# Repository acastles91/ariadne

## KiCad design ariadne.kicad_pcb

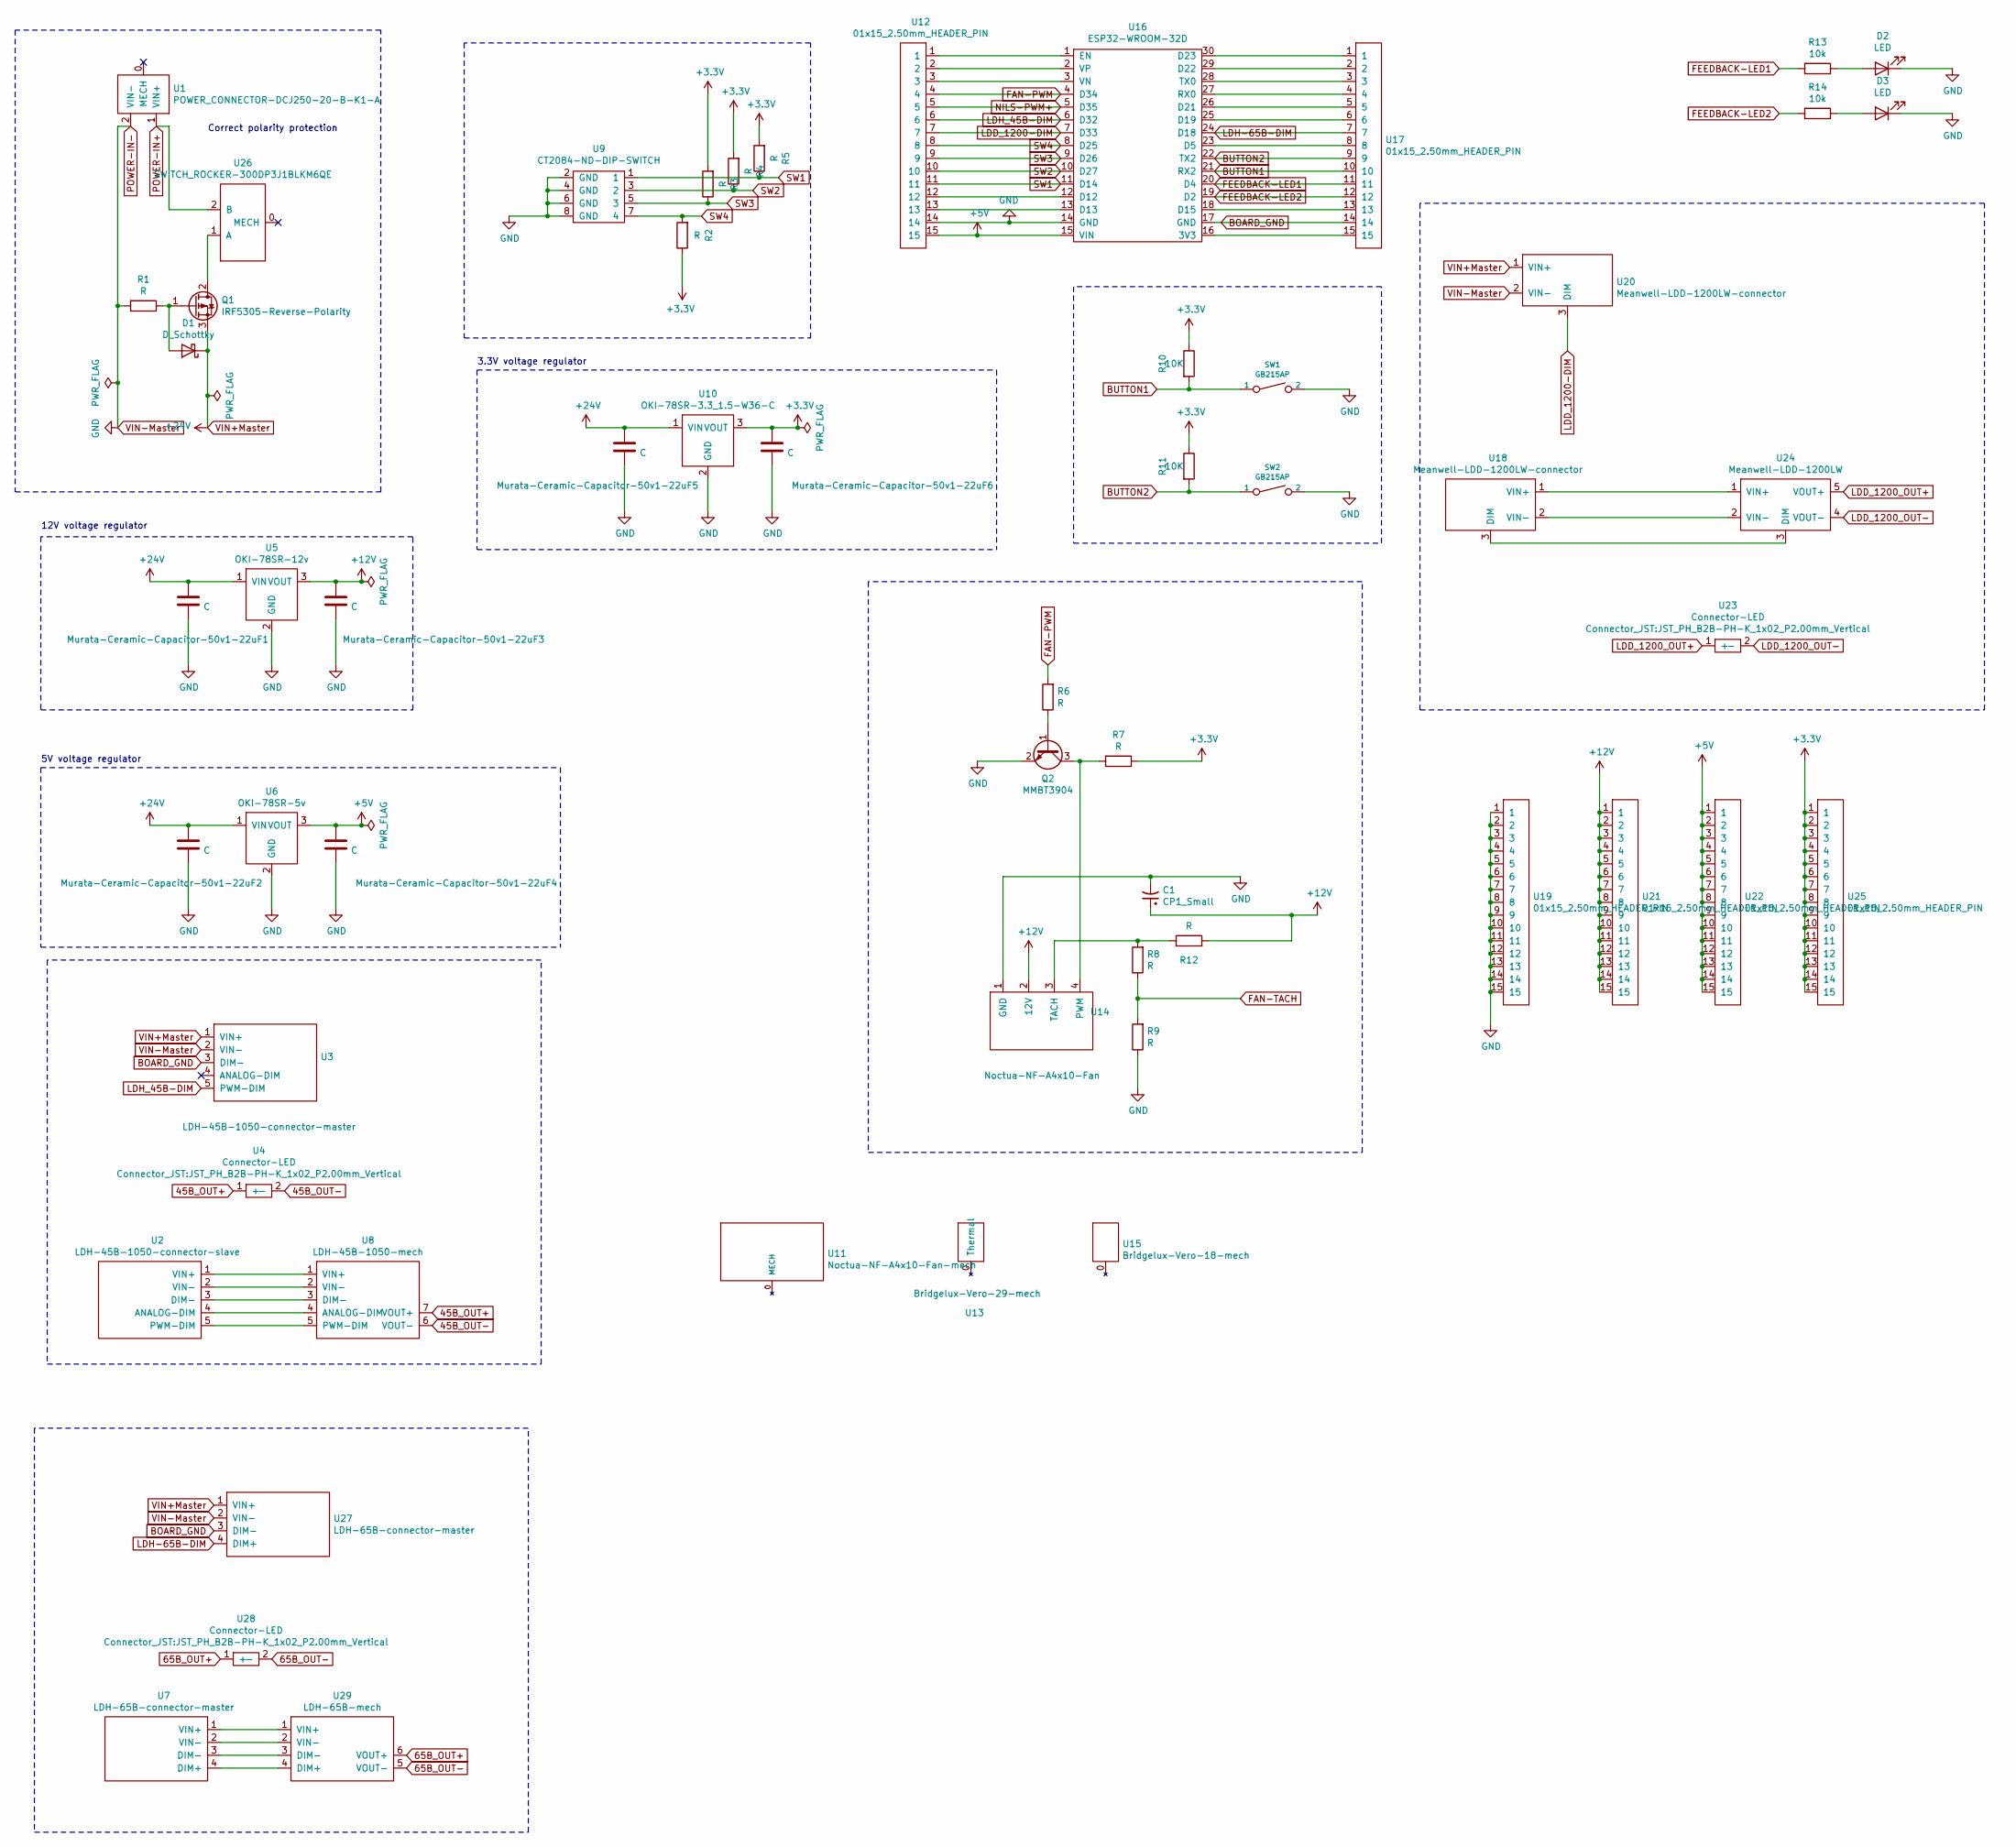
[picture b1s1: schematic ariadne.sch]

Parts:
C1: CP1_Small; CP_Radial_D5.0mm_P2.00mm
D1: D_Schottky; D_DO-41_SOD81_P7.62mm_Horizontal
D2, D3: LED; LED_D3.0mm_Horizontal_O1.27mm_Z2.0mm
Murata-Ceramic-Capacitor-50v1-22uF1, Murata-Ceramic-Capacitor-50v1-22uF2, Murata-Ceramic-Capacitor-50v1-22uF3, Murata-Ceramic-Capacitor-50v1-22uF4, Murata-Ceramic-Capacitor-50v1-22uF5, Murata-Ceramic-Capacitor-50v1-22uF6: C; C_Disc_D3.0mm_W1.6mm_P2.50mm
Q1: IRF5305-Reverse-Polarity; TO-220-3_Horizontal_TabDown
Q2: MMBT3904; TO-92
R1, R2, R3, R4, R5, R6, R7, R8, R9, R12: R; R_Axial_DIN0204_L3.6mm_D1.6mm_P7.62mm_Horizontal
R10, R11: 10K; R_Axial_DIN0204_L3.6mm_D1.6mm_P7.62mm_Horizontal
R13, R14: 10k; R_Axial_DIN0204_L3.6mm_D1.6mm_P7.62mm_Horizontal
SW1, SW2: GB215AP
U1: POWER_CONNECTOR-DCJ250-20-B-K1-A; POWER_JACK_DCJ250-20-B-K1-A
U2: LDH-45B-1050-connector-slave; Molex_Micro-Fit_3.0_43650-0500_1x05_P3.00mm_Horizontal
U3: LDH-45B-1050-connector-master; Molex_Micro-Fit_3.0_43650-0500_1x05_P3.00mm_Horizontal
U4, U23, U28: Connector-LED; JST_PH_B2B-PH-K_1x02_P2.00mm_Vertical
U5: OKI-78SR-12v; Converter_DCDC_muRata_OKI-78SR_Vertical
U6: OKI-78SR-5v; Converter_DCDC_muRata_OKI-78SR_Vertical
U7, U27: LDH-65B-connector-master; Molex_Micro-Fit_3.0_43650-0400_1x04_P3.00mm_Horizontal
U8: LDH-45B-1050-mech; MeanWell-LDH-45B-1050-ariadne
U9: CT2084-ND-DIP-SWITCH; SW_DIP_SPSTx04_Piano_CTS_Series194-4MSTN_W7.62mm_P2.54mm
U10: OKI-78SR-3.3_1.5-W36-C; Converter_DCDC_muRata_OKI-78SR_Vertical
U11: Noctua-NF-A4x10-Fan-mech; Noctua-NF-A4x10
U12, U17, U19, U21, U22, U25: 01x15_2.50mm_HEADER_PIN; PinHeader_1x15_P2.54mm_Vertical
U13: Bridgelux-Vero-29-mech; Vero-29-mech
U14: Noctua-NF-A4x10-Fan; Molex_Micro-Fit_3.0_43650-0400_1x04_P3.00mm_Horizontal
U15: Bridgelux-Vero-18-mech; Vero-18-mech
U16: ESP32-WROOM-32D; ESP32-DEVKIT
U18, U20: Meanwell-LDD-1200LW-connector; Molex_Micro-Fit_3.0_43650-0300_1x03_P3.00mm_Horizontal
U24: Meanwell-LDD-1200LW; Meanwell-LDD-1xxxL
U26: SWITCH_ROCKER-300DP3J1BLKM6QE
U29: LDH-65B-mech; MeanWell-LDH-65

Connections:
45B_OUT+: U4.1 (+), U8.7 (VOUT+)
45B_OUT-: U4.2 (-), U8.6 (VOUT-)
65B_OUT+: U28.1 (+), U29.6 (VOUT+)
65B_OUT-: U28.2 (-), U29.5 (VOUT-)
+3V3: Murata-Ceramic-Capacitor-50v1-22uF6.1, R2.1, R3.2, R4.2, R5.2, R7.1, R10.1, R11.1, U10.3 (VOUT), U25.1, U25.2, U25.3, U25.4, U25.5, U25.6, U25.7, U25.8, U25.9, U25.10, U25.11, U25.12, U25.13, U25.14, U25.15; also elsewhere on the board
+5V: Murata-Ceramic-Capacitor-50v1-22uF4.1, U6.3 (VOUT), U12.15, U16.15 (VIN), U22.1, U22.2, U22.3, U22.4, U22.5, U22.6, U22.7, U22.8, U22.9, U22.10, U22.11, U22.12, U22.13, U22.14, U22.15; also elsewhere on the board
+12V: C1.1, Murata-Ceramic-Capacitor-50v1-22uF3.1, R12.2, U5.3 (VOUT), U14.2 (12V), U21.1, U21.2, U21.3, U21.4, U21.5, U21.6, U21.7, U21.8, U21.9, U21.10, U21.11, U21.12, U21.13, U21.14, U21.15; also elsewhere on the board
BOARD_GND: U3.3 (DIM-), U16.17 (GND), U17.14, U27.3 (DIM-)
BUTTON1: R10.2, SW1.1, U16.21 (RX2), U17.10
BUTTON2: R11.2, SW2.1, U16.22 (TX2), U17.9
FAN-PWM: R6.2, U12.4, U16.4 (D34)
FAN-TACH: R8.1, R9.2
FEEDBACK-LED1: R13.2, U16.20 (D4), U17.11
FEEDBACK-LED2: R14.2, U16.19 (D2), U17.12
LDD_1200-DIM: U12.7, U16.7 (D33), U20.3 (DIM)
LDD_1200_OUT+: U23.1 (+), U24.5 (VOUT+)
LDD_1200_OUT-: U23.2 (-), U24.4 (VOUT-)
LDH-65B-DIM: U16.24 (D18), U17.7, U27.4 (DIM+)
LDH_45B-DIM: U3.5 (PWM-DIM), U12.6, U16.6 (D32)
NILS-PWM+: U12.5, U16.5 (D35)
unnamed: D1.2 (A), Q1.1 (G), R1.1
unnamed: D2.2 (A), R13.1
unnamed: D3.2 (A), R14.1
unnamed: Q1.2 (D), U26.1 (A)
unnamed: Q2.1 (B), R6.1
unnamed: Q2.3 (C), R7.2, U14.4 (PWM)
unnamed: R8.2, R12.1, U14.3 (TACH)
unnamed: U2.1 (VIN+), U8.1 (VIN+)
unnamed: U2.2 (VIN-), U8.2 (VIN-)
unnamed: U2.3 (DIM-), U8.3 (DIM-)
unnamed: U2.4 (ANALOG-DIM), U8.4 (ANALOG-DIM)
unnamed: U2.5 (PWM-DIM), U8.5 (PWM-DIM)
unnamed: U12.1, U16.1 (EN)
unnamed: U12.2, U16.2 (VP)
unnamed: U12.3, U16.3 (VN)
unnamed: U12.12, U16.12 (D12)
unnamed: U12.13, U16.13 (D13)
unnamed: U16.16 (3V3), U17.15
unnamed: U16.18 (D15), U17.13
unnamed: U16.23 (D5), U17.8
unnamed: U16.25 (D19), U17.6
unnamed: U16.26 (D21), U17.5
unnamed: U16.27 (RX0), U17.4
unnamed: U16.28 (TX0), U17.3
unnamed: U16.29 (D22), U17.2
unnamed: U16.30 (D23), U17.1
unnamed: U18.1 (VIN+), U24.1 (VIN+)
unnamed: U18.2 (VIN-), U24.2 (VIN-)
unnamed: U18.3 (DIM), U24.3 (DIM)
unnamed: U7.1 (VIN+), U29.1 (VIN+)
unnamed: U7.2 (VIN-), U29.2 (VIN-)
unnamed: U7.3 (DIM-), U29.3 (DIM-)
unnamed: U7.4 (DIM+), U29.4 (DIM+)
POWER-IN+: U1.1 (VIN+), U26.2 (B)
POWER-IN-: C1.2, D2.1 (K), D3.1 (K), Murata-Ceramic-Capacitor-50v1-22uF1.2, Murata-Ceramic-Capacitor-50v1-22uF2.2, Murata-Ceramic-Capacitor-50v1-22uF3.2, Murata-Ceramic-Capacitor-50v1-22uF4.2, Murata-Ceramic-Capacitor-50v1-22uF5.2, Murata-Ceramic-Capacitor-50v1-22uF6.2, Q2.2 (E), R1.2, R9.1, SW1.2, SW2.2, U1.2 (VIN-), U3.2 (VIN-), U5.2 (GND), U6.2 (GND), U9.2 (GND), U9.4 (GND), U9.6 (GND), U9.8 (GND), U10.2 (GND), U12.14, U14.1 (GND), U16.14 (GND), U19.1, U19.2, U19.3, U19.4, U19.5, U19.6, U19.7, U19.8, U19.9, U19.10, U19.11, U19.12, U19.13, U19.14, U19.15, U20.2 (VIN-), U27.2 (VIN-); also elsewhere on the board
SW1: R5.1, U9.1, U12.11, U16.11 (D14)
SW2: R4.1, U9.3 (2), U12.10, U16.10 (D27)
SW3: R3.1, U9.5 (3), U12.9, U16.9 (D26)
SW4: R2.2, U9.7 (4), U12.8, U16.8 (D25)
VIN+Master: D1.1 (K), Murata-Ceramic-Capacitor-50v1-22uF1.1, Murata-Ceramic-Capacitor-50v1-22uF2.1, Murata-Ceramic-Capacitor-50v1-22uF5.1, Q1.3 (S), U3.1 (VIN+), U5.1 (VIN), U6.1 (VIN), U10.1 (VIN), U20.1 (VIN+), U27.1 (VIN+)

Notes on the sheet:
Correct polarity protection
12V voltage regulator
5V voltage regulator
3.3V voltage regulator

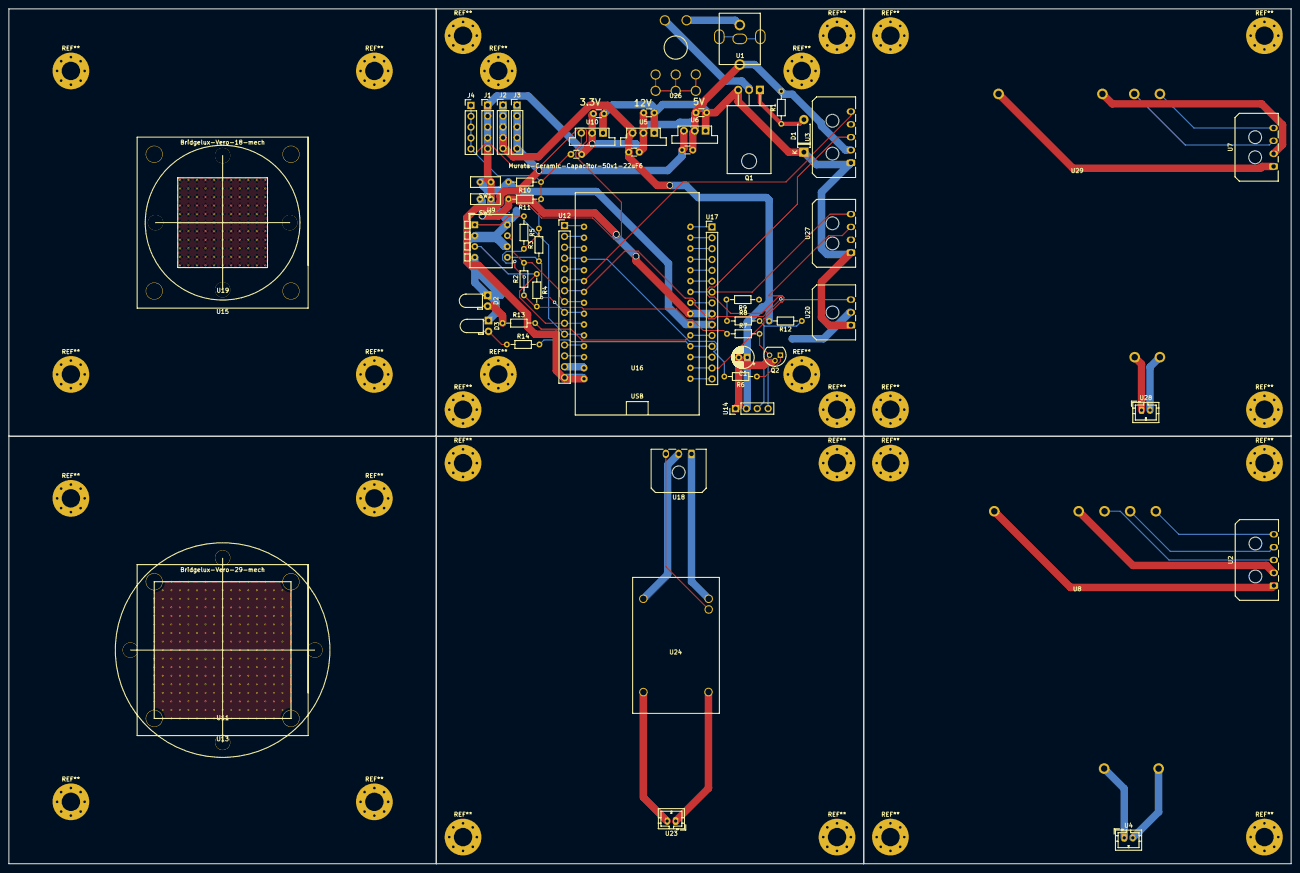
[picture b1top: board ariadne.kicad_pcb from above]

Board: 2 copper layers, 300.0 x 200.0 mm, 58 parts (0 on the bottom side), 60 nets.

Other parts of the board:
J1, J2, J3, J4: Conn_01x05_Male; PinHeader_1x05_P2.54mm_Vertical

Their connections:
+3V3: J4.1, J4.2, J4.3, J4.4, J4.5; also elsewhere on the board
+5V: J3.1, J3.2, J3.3, J3.4, J3.5; also elsewhere on the board
+12V: J2.1, J2.2, J2.3, J2.4, J2.5; also elsewhere on the board
POWER-IN-: J1.1, J1.2, J1.3, J1.4, J1.5; also elsewhere on the board

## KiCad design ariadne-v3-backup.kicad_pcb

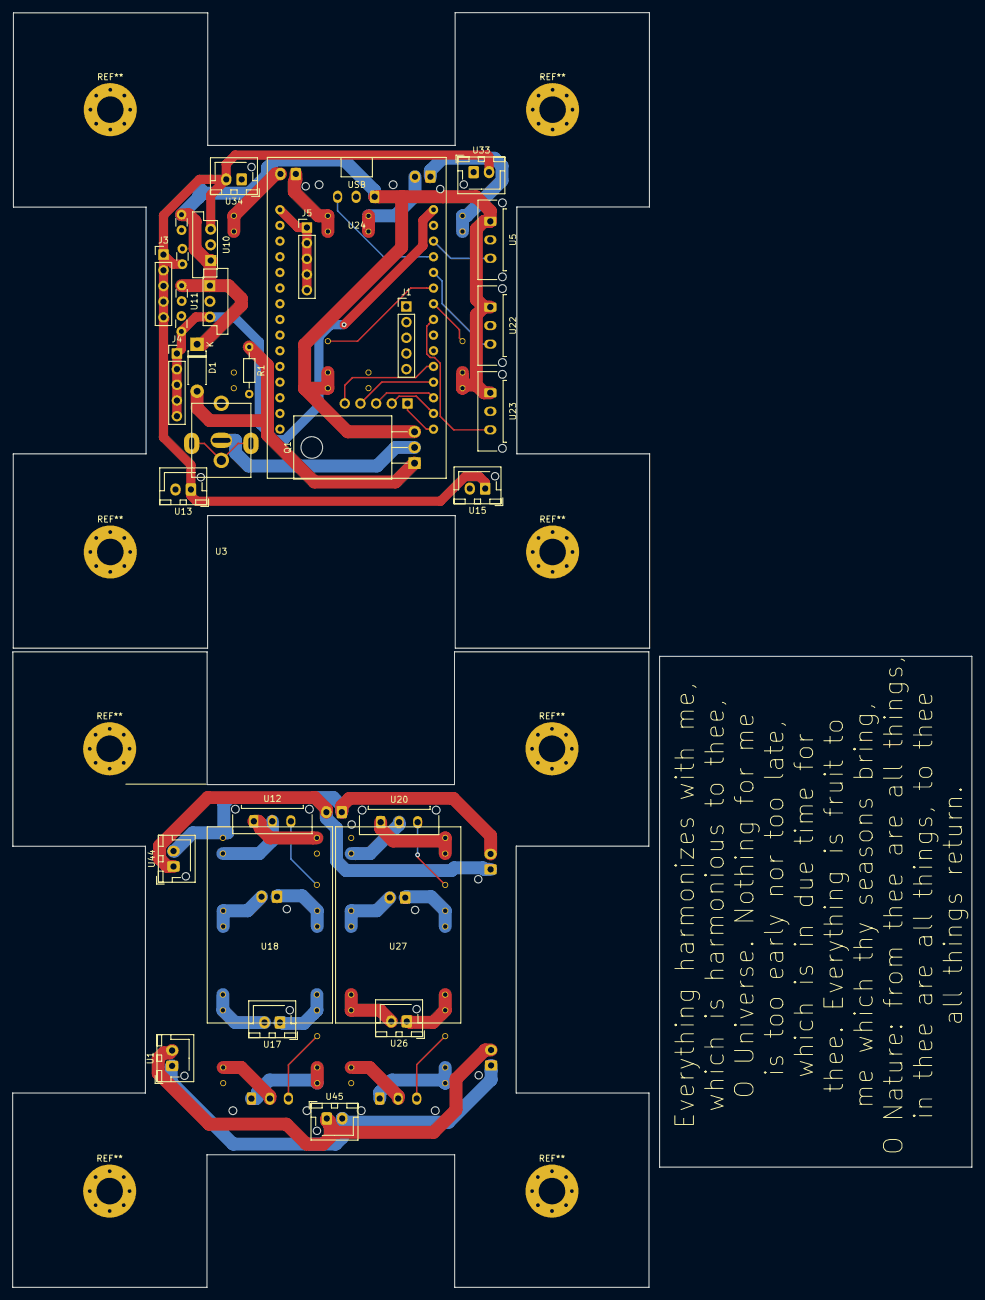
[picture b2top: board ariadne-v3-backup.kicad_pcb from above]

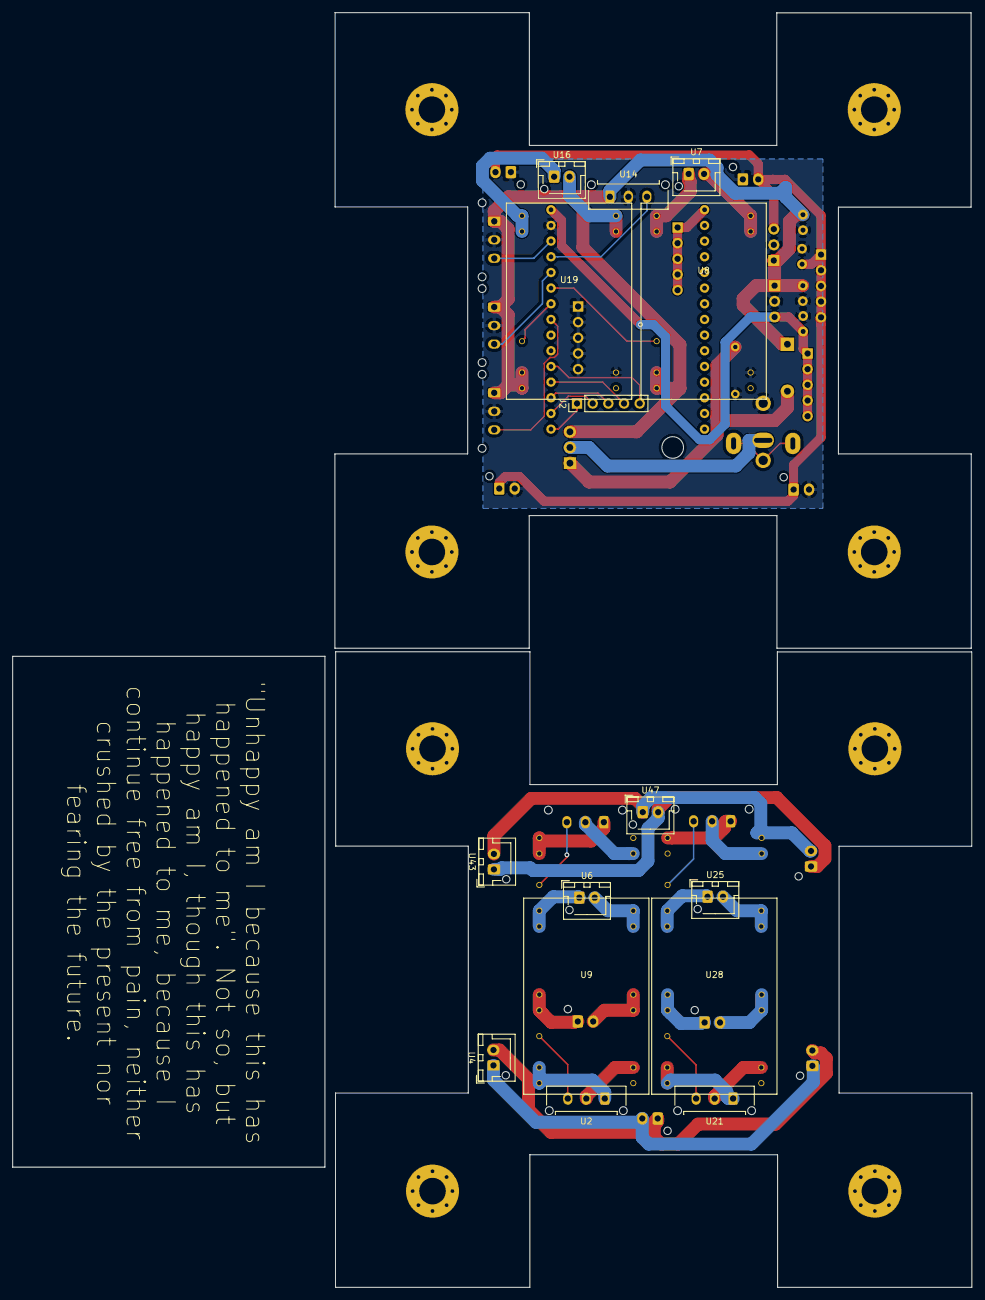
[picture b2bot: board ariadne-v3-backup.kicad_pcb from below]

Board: 2 copper layers, 155.5 x 206.6 mm, 46 parts (15 on the bottom side), 46 nets.

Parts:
D1: D_Zener-10V; D_DO-41_SOD81_P7.62mm_Horizontal
J1, J2, J3, J4, J5: Conn_01x05_Male; PinHeader_1x05_P2.54mm_Vertical
Murata-Ceramic-Capacitor-50v1-22uF1, Murata-Ceramic-Capacitor-50v1-22uF2, Murata-Ceramic-Capacitor-50v1-22uF3, Murata-Ceramic-Capacitor-50v1-22uF4: C; C_Disc_D3.0mm_W1.6mm_P2.50mm
Q1: IRF5305-Reverse-Polarity; TO-220-3_Horizontal_TabDown
R1: 100K; R_Axial_DIN0204_L3.6mm_D1.6mm_P7.62mm_Horizontal
U1, U4, U33, U34, U43, U44: Noctua-NF-A4x10-Simple-Fan-ariadne; JST_XH_B2B-XH-AM_1x02_P2.50mm_Vertical
U2, U5, U12, U14, U20, U21, U22, U23: Meanwell-LDD-1200LW-connector; Molex_Micro-Fit_3.0_43650-0315_1x03_P3.00mm_Vertical
U3: POWER_CONNECTOR-DCJ250-20-B-K1-A; POWER_JACK_DCJ250-20-B-K1-A
U6, U7, U16, U17, U25, U26: Connector-LED; JST_XH_B2B-XH-AM_1x02_P2.50mm_Vertical
U8, U9, U18, U19, U27, U28: Meanwell-LDD-1200LW; Meanwell-LDD-1xxxL
U10: OKI-78SR-12v; Converter_DCDC_muRata_OKI-78SR_Vertical
U11: OKI-78SR-5v; Converter_DCDC_muRata_OKI-78SR_Vertical
U13, U15: 12v-Connector; JST_XH_B2B-XH-AM_1x02_P2.50mm_Vertical
U24: ESP32-WROOM-32D; ESP32-DEVKIT
U45, U47: 12v-Connector_copy; JST_XH_B2B-XH-AM_1x02_P2.50mm_Vertical

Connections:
+3V3: J5.1, J5.2, J5.3, J5.4, J5.5, U24.16
+5V: J4.1, J4.2, J4.3, J4.4, J4.5, Murata-Ceramic-Capacitor-50v1-22uF4.1, U11.3, U24.15
+12V: J3.1, J3.2, J3.3, J3.4, J3.5, Murata-Ceramic-Capacitor-50v1-22uF3.1, U10.3, U13.1, U15.1, U33.2, U34.2
DIM-1: U5.3, U24.13
DIM-2: U14.3, U24.12
DIM-3: U22.3, U24.11
DIM-4: U8.21, U24.10
DIM-5: U19.21, U24.9
DIM-6: U23.3, U24.8
FAN1+: U43.2, U44.2, U47.1
FAN1-: U43.1, U44.1, U47.2
FAN2+: U1.2, U4.2, U45.1
FAN2-: U1.1, U4.1, U45.2
LDD_1-OUT+: U6.1, U9.13, U9.14
LDD_1-OUT-: U6.2, U9.11, U9.12
LDD_2-OUT+: U17.1, U18.13, U18.14
LDD_2-OUT-: U17.2, U18.11, U18.12
LDD_3-OUT+: U26.1, U27.13, U27.14
LDD_3-OUT-: U26.2, U27.11, U27.12
LDD_4-OUT+: U7.1, U8.13, U8.14
LDD_4-OUT-: U7.2, U8.11, U8.12
LDD_5-OUT+: U16.1, U19.13, U19.14
LDD_5-OUT-: U16.2, U19.11, U19.12
LDD_6-OUT+: U25.1, U28.13, U28.14
LDD_6-OUT-: U25.2, U28.11, U28.12
unnamed: D1.2, Q1.1, R1.1
unnamed: J2.1, U24.1
unnamed: J2.2, U24.2
unnamed: J2.3, U24.3
unnamed: J2.4, U24.4
unnamed: J2.5, U24.5
unnamed: U2.1, U9.23, U9.24
unnamed: U2.2, U9.2
unnamed: U2.3, U9.21
unnamed: U12.1, U18.23, U18.24
unnamed: U12.2, U18.2
unnamed: U12.3, U18.21
unnamed: U20.1, U27.23, U27.24
unnamed: U20.2, U27.2
unnamed: U20.3, U27.21
unnamed: U21.1, U28.23, U28.24
unnamed: U21.2, U28.2
unnamed: U21.3, U28.21
POWER-IN+: Q1.2, U3.1
POWER-IN-: J1.1, J1.2, J1.3, J1.4, J1.5, Murata-Ceramic-Capacitor-50v1-22uF1.2, Murata-Ceramic-Capacitor-50v1-22uF2.2, Murata-Ceramic-Capacitor-50v1-22uF3.2, Murata-Ceramic-Capacitor-50v1-22uF4.2, R1.2, U3.2, U5.2, U8.2, U10.2, U11.2, U13.2, U14.2, U15.2, U19.2, U22.2, U23.2, U24.14, U33.1, U34.1
VIN+Master1: D1.1, Murata-Ceramic-Capacitor-50v1-22uF1.1, Murata-Ceramic-Capacitor-50v1-22uF2.1, Q1.3, U5.1, U8.23, U8.24, U10.1, U11.1, U14.1, U19.23, U19.24, U22.1, U23.1

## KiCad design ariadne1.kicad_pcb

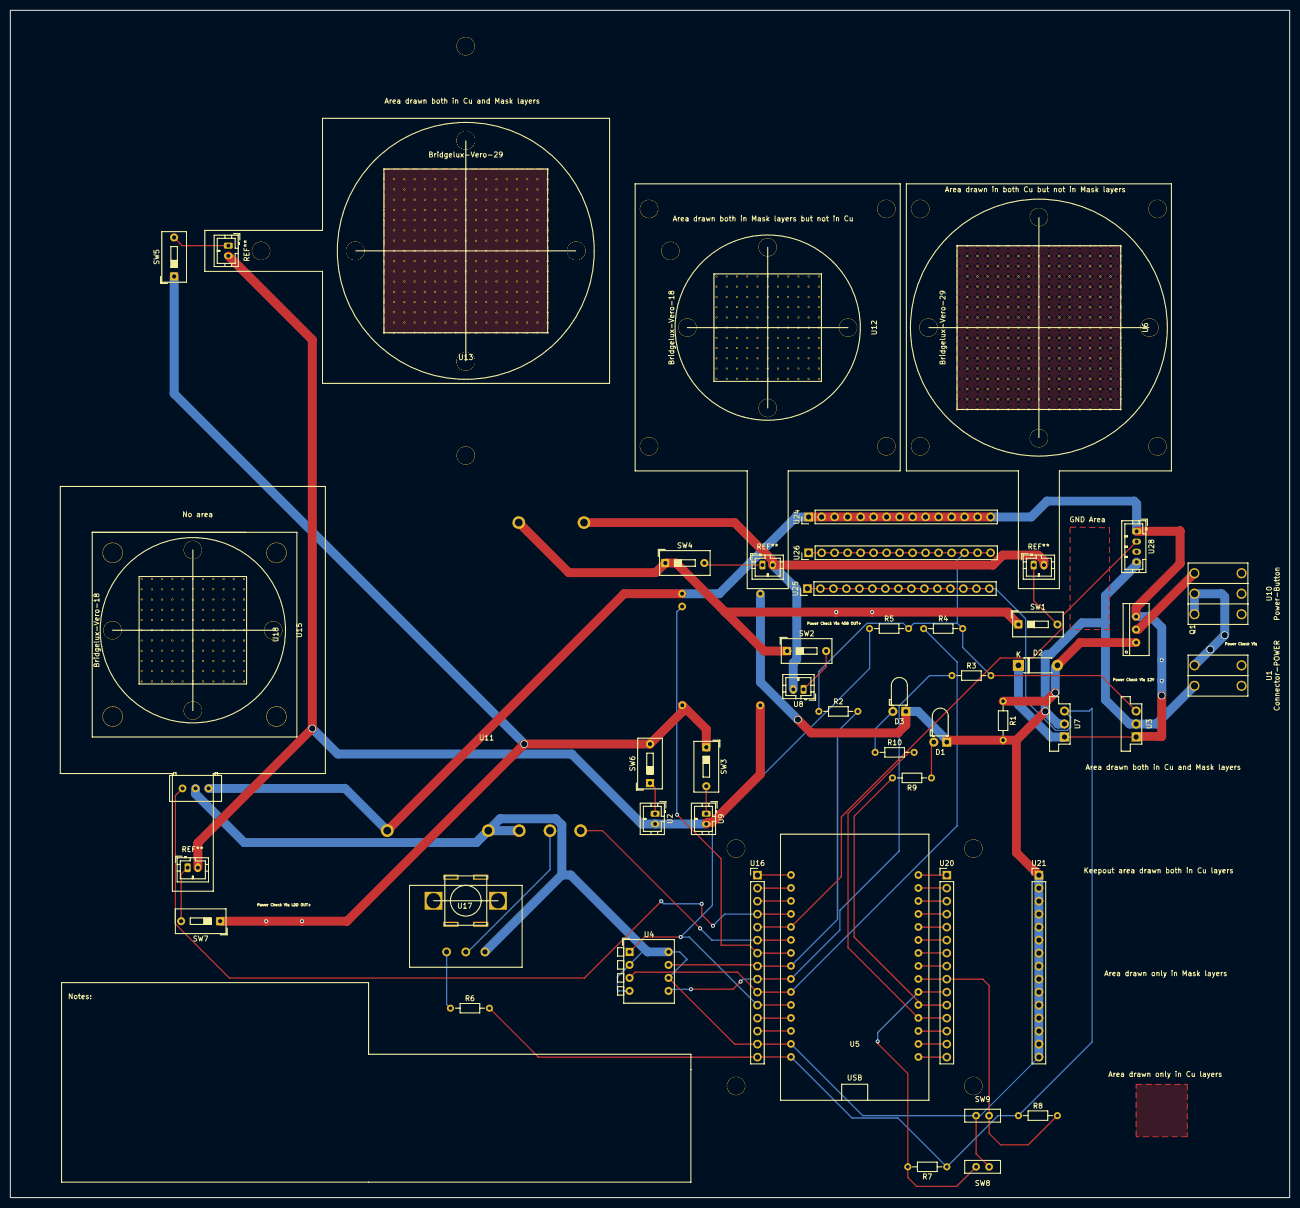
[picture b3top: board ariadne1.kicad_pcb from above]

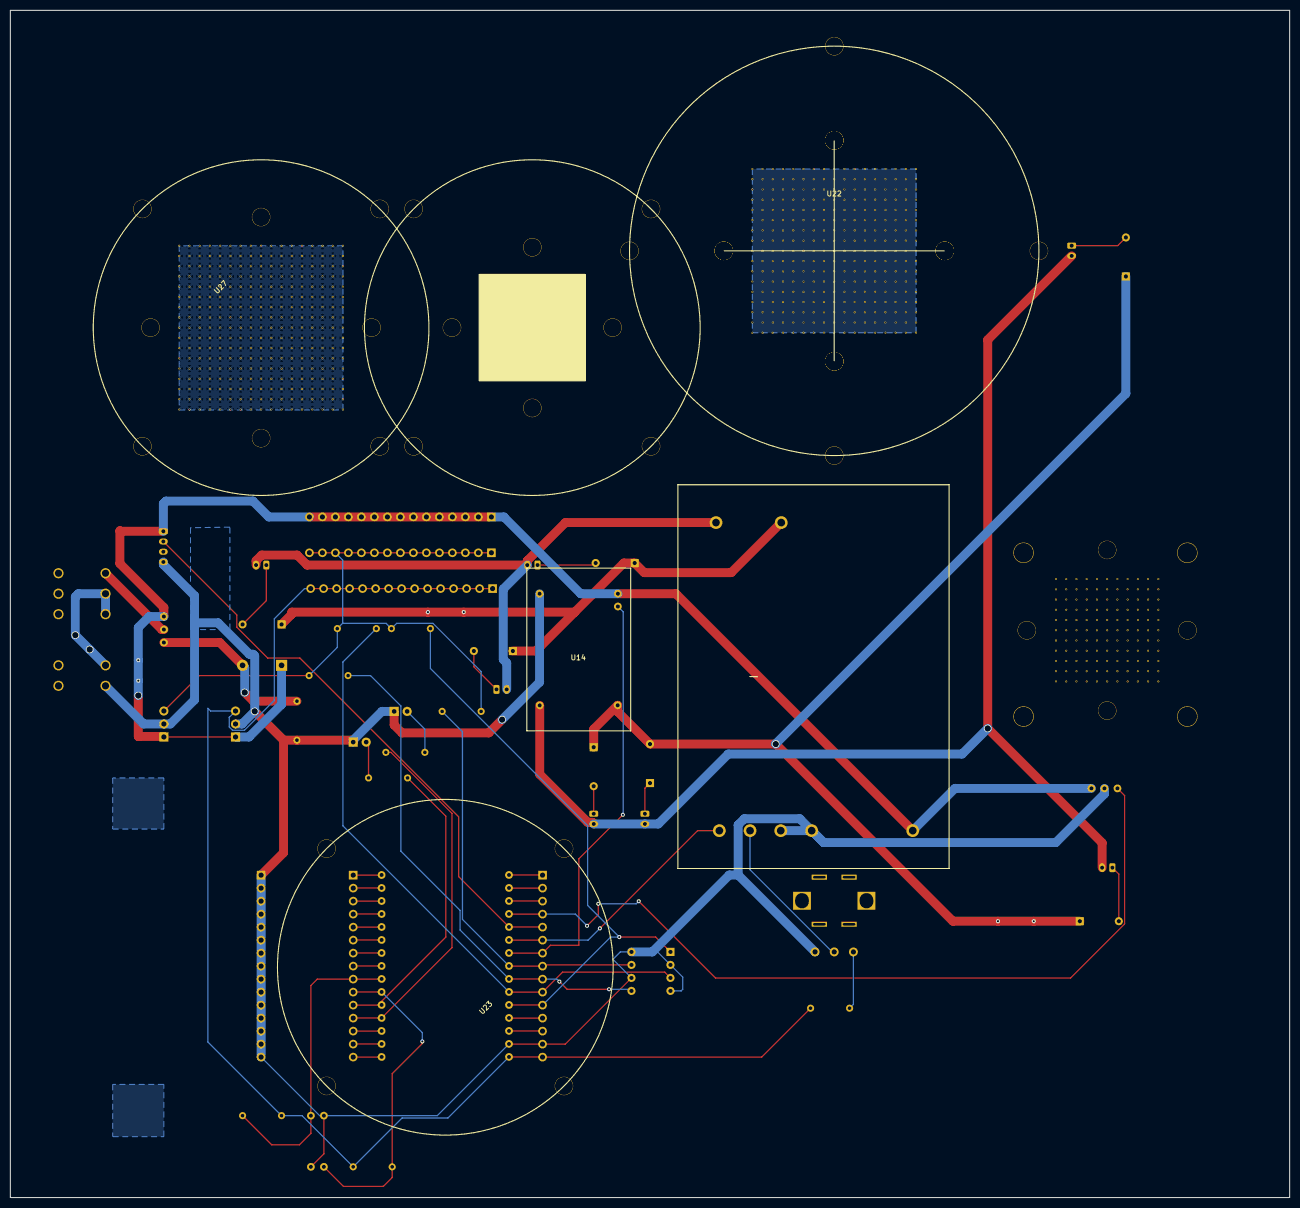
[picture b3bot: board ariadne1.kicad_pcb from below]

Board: 2 copper layers, 250.0 x 232.0 mm, 51 parts (5 on the bottom side), 50 nets.

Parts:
D1, D3: LED; LED_D3.0mm_Horizontal_O1.27mm_Z2.0mm
D2: D_Schottky; D_DO-41_SOD81_P7.62mm_Horizontal
Q1: IRF5305-Reverse-Polarity; IRF5305
R1, R2, R3, R4, R5: R; R_Axial_DIN0204_L3.6mm_D1.6mm_P7.62mm_Horizontal
R6: 33k; R_Axial_DIN0204_L3.6mm_D1.6mm_P7.62mm_Horizontal
R7, R8: 10K; R_Axial_DIN0204_L3.6mm_D1.6mm_P7.62mm_Horizontal
R9, R10: 10k; R_Axial_DIN0204_L3.6mm_D1.6mm_P7.62mm_Horizontal
SW1, SW2, SW3, SW4, SW5, SW6, SW7: SW_DIP_x01; SW_DIP_SPSTx01_Slide_9.78x4.72mm_W7.62mm_P2.54mm
SW8, SW9: GB215AP
U1: Connector-POWER; WAGO_PCB_Klemme_2Pol
U2: Connector-LED-NILS; JST_PH_B2B-PH-K_1x02_P2.00mm_Vertical
U3: OKI-78SR-3.3_1.5-W36-C; Converter_DCDC_muRata_OKI-78SR_Vertical
U4: CT2084-ND-DIP-SWITCH; SW_DIP_SPSTx04_Piano_CTS_Series194-4MSTN_W7.62mm_P2.54mm
U5: ESP32-WROOM-32D; ESP32-DEVKIT
U6, U13: Bridgelux-Vero-29; Vero-29
U7: OKI-78SR-5v; Converter_DCDC_muRata_OKI-78SR_Vertical
U8, U9: Connector-LED; JST_PH_B2B-PH-K_1x02_P2.00mm_Vertical
U10: Power-Button; WAGO_PCB_Klemme_3Pol
U11: LDH-45B-1050; MeanWell-LDH-45B-1050
U12, U15: Bridgelux-Vero-18; Vero-18
U14: Meanwell-LDD-1200LW; Meanwell-LDD-1xxxL
U16, U20, U21, U24, U25, U26: 01x15_2.50mm_HEADER_PIN; PinHeader_1x15_P2.54mm_Vertical
U17: POTENTIOMETER; PDB12-H4301-Potentiometer
U18: Noctua-NF-A4x10-Fan; Noctua-NF-A4x10
U19, U23, U27: Heatsink-HP20S-CALBL-001
U22: Heatsink-NX301117
U28: Nils-Booster; JST_PH_B4B-PH-K_1x04_P2.00mm_Vertical

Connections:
45B_OUT+: SW1.1, SW2.1, SW4.1, U11.7
45B_OUT-: U6.2, U8.2, U11.6, U12.2
+3V3: R2.1, R3.2, R4.2, R5.2, U3.3, U26.1, U26.2, U26.3, U26.4, U26.5, U26.6, U26.7, U26.8, U26.9, U26.10, U26.11, U26.12, U26.13, U26.14, U26.15
+5V: R6.2, R7.1, R8.1, U5.15, U7.3, U16.15, U25.1, U25.2, U25.3, U25.4, U25.5, U25.6, U25.7, U25.8, U25.9, U25.10, U25.11, U25.12, U25.13, U25.14, U25.15
+12V: D2.1, Q1.3, U3.1, U7.1, U11.5, U14.1, U18.3, U24.1, U24.2, U24.3, U24.4, U24.5, U24.6, U24.7, U24.8, U24.9, U24.10, U24.11, U24.12, U24.13, U24.14, U24.15, U28.1
BUTTON1: R7.2, SW8.1, U5.21, U20.10
BUTTON2: R8.2, SW9.1, U5.22, U20.9
FAN-PWM: U5.4, U16.4, U18.1
FEEDBACK-LED1: R9.2, U5.20, U20.11
FEEDBACK-LED2: R10.2, U5.19, U20.12
LDD_1200-DIM: U5.7, U14.3, U16.7
LDD_1200_OUT+: SW3.1, SW5.1, SW6.2, SW7.1, U14.5
LDD_1200_OUT-: U2.2, U9.2, U13.2, U14.4, U15.2
LDH_45B-DIM: U5.6, U11.1, U16.6
NILS-PWM+: U5.5, U16.5, U28.2
unnamed: D1.2, R9.1
unnamed: D2.2, Q1.1, R1.1
unnamed: D3.2, R10.1
unnamed: Q1.2, U10.1
unnamed: R6.1, U17.1
unnamed: SW1.2, U6.1
unnamed: SW2.2, U8.1
unnamed: SW3.2, U9.1
unnamed: SW4.2, U12.1
unnamed: SW5.2, U13.1
unnamed: SW6.1, U2.1
unnamed: SW7.2, U15.1
unnamed: U5.1, U16.1
unnamed: U5.2, U16.2
unnamed: U5.3, U16.3
unnamed: U5.12, U16.12
unnamed: U5.13, U16.13
unnamed: U5.30, U20.1
unnamed: U5.29, U20.2
unnamed: U5.28, U20.3
unnamed: U5.27, U20.4
unnamed: U5.26, U20.5
unnamed: U5.25, U20.6
unnamed: U5.24, U20.7
unnamed: U5.23, U20.8
unnamed: U5.18, U20.13
unnamed: U5.17, U20.14
unnamed: U5.16, U20.15
POTI-45-B: U11.2, U17.2
POWER-IN+: U1.1, U10.2, U10.3
POWER-IN-: D1.1, D3.1, R1.2, SW8.2, SW9.2, U1.2, U3.2, U4.2, U4.4, U4.6, U4.8, U5.14, U7.2, U11.3, U11.4, U14.2, U16.14, U17.3, U18.2, U21.1, U21.2, U21.3, U21.4, U21.5, U21.6, U21.7, U21.8, U21.9, U21.10, U21.11, U21.12, U21.13, U21.14, U21.15, U28.3, U28.4
SW1: R5.1, U4.1, U5.11, U16.11
SW2: R4.1, U4.3, U5.10, U16.10
SW3: R3.1, U4.5, U5.9, U16.9
SW4: R2.2, U4.7, U5.8, U16.8

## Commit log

2020-10-15 First
2020-11-05 finalized first pcb
2020-11-06 second version, in progress
2020-11-06 BOM made at carla's
2020-11-10 second version ready for layout
2020-11-20 Second version ordered
2020-11-20 Second version with code
2020-11-23 Ready for third version
2020-11-25 Before carla leaves for HK
2020-12-11 third version ready for production
2020-12-11 now for real
2021-01-06 Fourth version, footprint of LED driver was flipped. Gave some cleareance to the ground plane, re arranged some paths.
